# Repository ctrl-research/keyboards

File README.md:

# keyboards
Schematics, pcbs, layout files for all my keyboard projects

## Structure

- `design/` — original keyboard designs, one folder per board with
  `layout/` (KLE, keymap, VIA), `pcb/` (KiCad), `case/` (3DP CAD), and
  `firmware/` (QMK/VIA builds) inside
  - [`gemini/`](design/gemini/) — split staggered 40% that docks into a regular 40%
- `commissions/` — VIA/layout files for boards built for others
- `docs/` — GitHub Pages site with interactive design docs, deployed by
  [`.github/workflows/pages.yml`](.github/workflows/pages.yml) on every push
  to `main` that touches `docs/` (one-time setup: Settings → Pages → Source →
  GitHub Actions)

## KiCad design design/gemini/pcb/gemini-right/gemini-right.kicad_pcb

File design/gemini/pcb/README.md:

# pcb

KiCad projects for the Gemini PCBs — one board per half.

**Architecture (rev A): one controller.** A single Raspberry Pi Pico on the
left half (header-mounted on the back, ~2.5 mm standoff); the right half is
passive with an MCP23017 I/O expander. The halves link over **USB-C
carrying I2C** (3V3/SDA/SCL/GND — any USB 2.0 C-to-C cable). Full pin map,
link wiring, socket-DNP keys and BOM: [`pinmap.md`](pinmap.md).

## Generated projects

- [`gemini-left/`](gemini-left/), [`gemini-right/`](gemini-right/) —
  generated `.kicad_pcb` per half: all footprints placed, nets assigned,
  seam edge cuts drawn. **Unrouted** — routing is interactive work.
- [`gemini-panel/`](gemini-panel/) — **production panel** for JLCPCB/PCBWay:
  both halves in one board, joined along their straight *outer* edges at
  x = 0 with a single **V-score** snap line (the stepped seam can't be
  V-scored — it faces outward and is routed normally). Refs and nets are
  prefixed `L_`/`R_`. Route the individual halves first, then regenerate —
  or route the panel directly and it supersedes them. When ordering: pick
  "panel by customer", 2 designs, and note "V-cut where marked" in remarks.
  Snapped V-score edges land inside the case (the seam-inset walls cover
  all board edges), so no cosmetic cleanup matters.
- Regenerate with KiCad's bundled python (wx workaround included):

  ```
  /Applications/KiCad/KiCad.app/Contents/Frameworks/Python.framework/Versions/Current/bin/python3 tools/gen_kicad_boards.py
  ```

## Inputs (source of truth: `../layout/gemini_docked.kle.json`)

- [`tools/gen_pcb_data.py`](tools/) — derives everything below from the
  layout geometry; [`tools/gen_kicad_boards.py`](tools/) builds the boards.
- [`placement/*_placement.csv`](placement/) — switch centers in mm with
  matrix row/col (per-half origin at its top-left corner).
- [`placement/*_outline.csv`](placement/) — Edge.Cuts vertices in mm
  including the stepped docking seam (inset 1.45 mm from the key boundary —
  the case seam wall carries the true boundary) and the 8 mm rear brow
  (link ports live there). Left ≤ 127.14 × 84.2 mm, right ≤ 122.38 × 84.2 mm.
- [`kbplacer/*_matrix.kle.json`](kbplacer/) — KLE annotated with `row,col`
  legends for the [kbplacer](https://github.com/adamws/kicad-kbplacer)
  plugin.
- [`lib/gemini.pretty`](lib/) — vendored footprints (marbastlib hotswap +
  stabs, Pico, HRO USB-C, MCP23017/passives from KiCad stock) and 3D
  models; licenses in `lib/licenses/`.
- [`gemini.kicad_mod`](gemini.kicad_mod) — source logo artwork from
  bitmap2component (35.9 × 13.9 mm). [`tools/gen_logo_fp.py`](tools/)
  scales it to 6 mm tall and writes `lib/gemini.pretty/Logo_Gemini.kicad_mod`
  with its origin at the artwork centre; the board generator places that
  on **F.SilkS**, centred in the 8 mm rear brow (left x 58.81, right
  x 62.29, both at y −4). The brow's *back* face is full of ports and
  passives, so the front face is where the room is. 6 mm is the practical
  floor for the small "by: j6n" glyphs: it keeps the thinnest stroke at
  0.40 mm and the tightest enclosed counter at 0.22 mm, versus the
  0.15 mm silkscreen minimum JLCPCB/PCBWay quote.

## 3D exports

The docs page's **3D model tab** (`docs/gemini/#model`) renders the full
assembly — boards + case pieces, docked/split and exploded/assembled
(three.js; GLBs live in `docs/gemini/3d/`). Re-export after board changes:

```
kicad-cli pcb export glb --subst-models --include-tracks --include-pads \
  --include-zones --include-silkscreen --user-origin 119.0625x0mm \
  -o raw-left.glb gemini-left/gemini-left.kicad_pcb   # right: no origin arg
npx gltfpack -i raw-left.glb -o docs/gemini/3d/gemini-left.glb -cc -mi -si 0.4 -noq
```

(The +119.0625 mm origin shift puts both halves in one docked frame.
`-noq` matters: quantized output renders at the wrong scale in the viewer.
`--include-silkscreen` costs ~4 % file size and is what makes the brow
logo and the reference designators show up in the viewer.)

## Before fab (rev A checklist)

- [x] Route both boards (autorouted + USB-C escapes rebuilt by hand: the
      generated nested stitch fenced the inner nets on B.Cu, so each link
      /host connector now fans out through 0.6/0.3 vias to F.Cu; DRC: 0
      unconnected on both halves and the panel)
- [ ] Verify HRO USB-C pad↔pin mapping against the datasheet (incl. which
      pads are CC vs SBU — the LED chain crosses on CC)
- [ ] Verify SK6812 MINI-E pad order (assumed 1=VDD 2=DOUT 3=VSS 4=DIN)
- [ ] Host port TP1/TP2 pads: bridge to Pico underside TP3 (D+) / TP2 (D−)
      — decide jumper wires vs relocating pads under the TPs for spring pins
- [ ] Series resistors on link D± so a real charger/host can't hurt anything
- [ ] QMK: cap `RGB_MATRIX_MAXIMUM_BRIGHTNESS` (~120) — 43 LEDs at full
      white would far exceed a 500 mA USB 2.0 budget
- [ ] DRC: Pico pin rows sit at y=19.7 and y=37.5, in the corridors between
      switch rows on both faces — confirm clearances after any nudges
- [ ] Confirm J1 orientation (port opening must overhang the rear edge)
- [ ] Case: ~5 mm pocket under the Pico strip (~2 mm elsewhere), rear
      cutouts for both link ports, side cutout for the Pico micro-USB

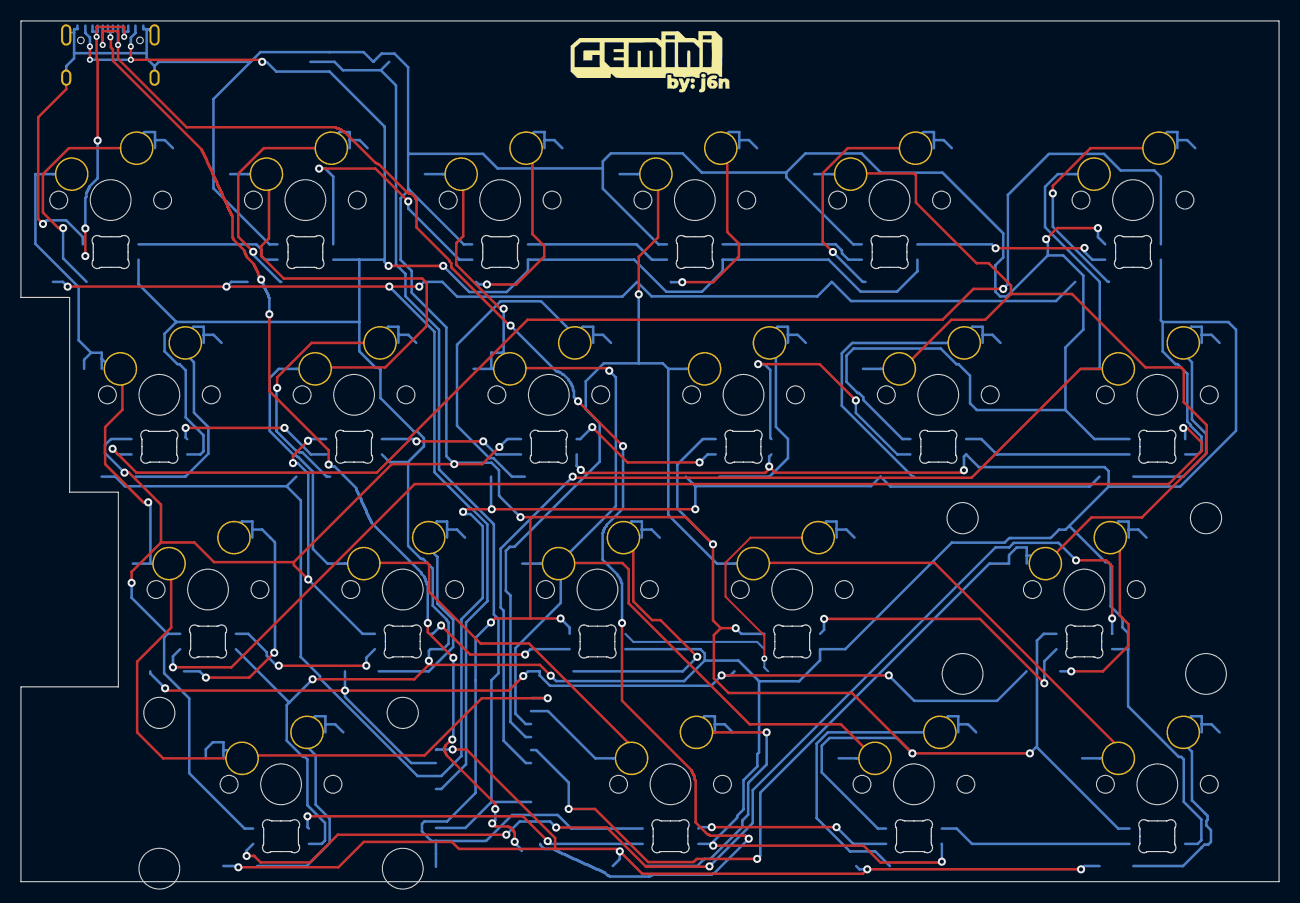
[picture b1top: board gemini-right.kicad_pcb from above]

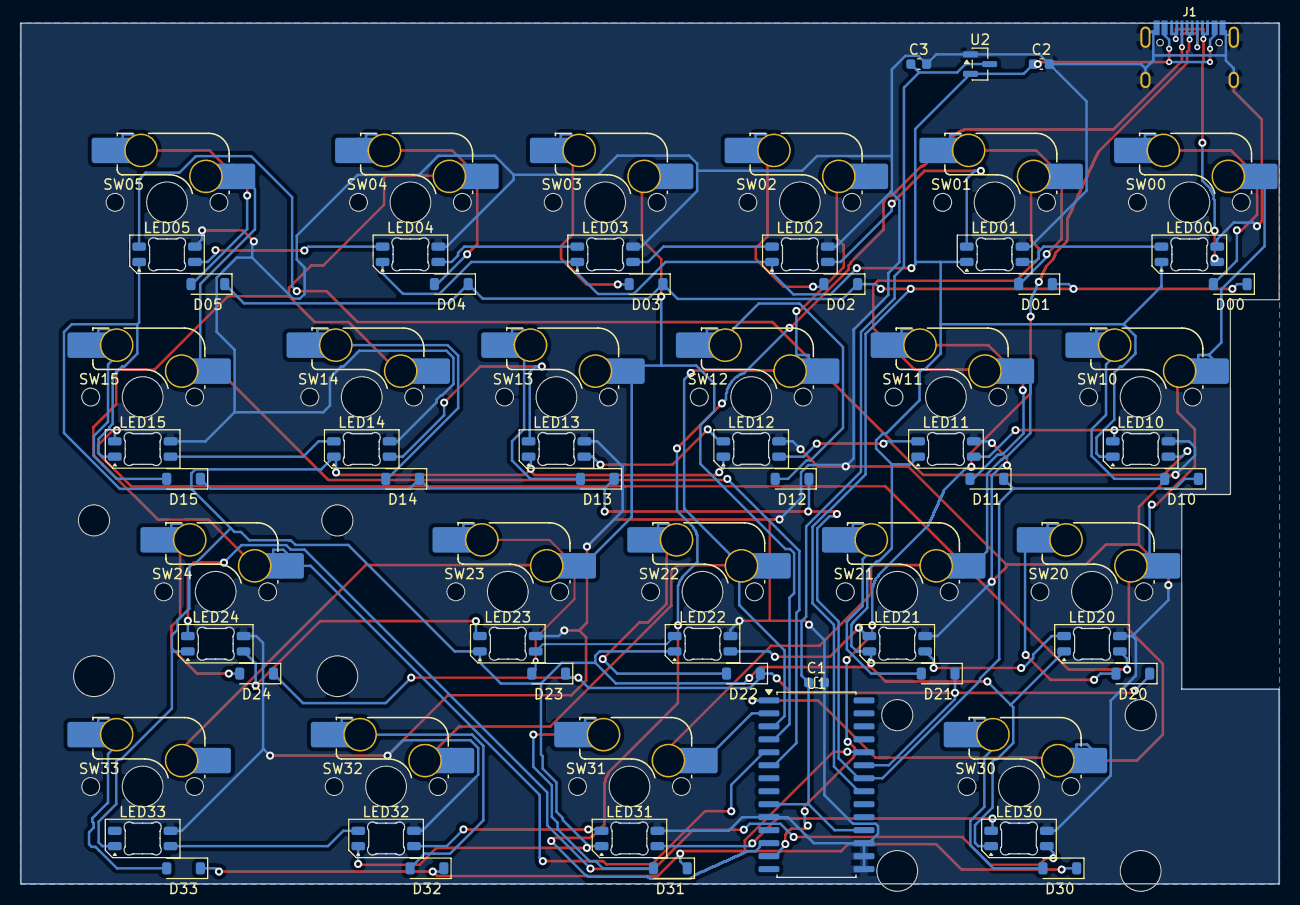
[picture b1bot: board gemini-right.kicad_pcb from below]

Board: 2 copper layers, 123.1 x 84.2 mm, 72 parts (69 on the bottom side), 57 nets.

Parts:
C1: 100nF; C_0603_1608Metric
C2, C3: 1uF; C_0603_1608Metric
D00, D01, D02, D03, D04, D05, D10, D11, D12, D13, D14, D15, D20, D21, D22, D23, D24, D30, D31, D32, D33: 1N4148W; D_SOD-123
G1: Logo_Gemini
J1: USB-C link; HRO-TYPE-C-31-M-12-Assembly
LED00, LED01, LED02, LED03, LED04, LED05, LED10, LED11, LED12, LED13, LED14, LED15, LED20, LED21, LED22, LED23, LED24, LED30, LED31, LED32, LED33: SK6812MINI-E; LED_SK6812MINI-E_3.2x2.8mm_P1.5mm_ReverseMount
ST_SW24: stab 2.0u; STAB_MX_2u
ST_SW30: stab 2.75u; STAB_MX_2.75u
SW00: Y; SW_MX_HS_CPG151101S11_1u
SW01: U; SW_MX_HS_CPG151101S11_1u
SW02: I; SW_MX_HS_CPG151101S11_1u
SW03: O; SW_MX_HS_CPG151101S11_1u
SW04: P; SW_MX_HS_CPG151101S11_1u
SW05: Bksp; SW_MX_HS_CPG151101S11_1.5u
SW10: H; SW_MX_HS_CPG151101S11_1u
SW11: J; SW_MX_HS_CPG151101S11_1u
SW12: K; SW_MX_HS_CPG151101S11_1u
SW13: L; SW_MX_HS_CPG151101S11_1u
SW14: ;; SW_MX_HS_CPG151101S11_1u
SW15: Enter; SW_MX_HS_CPG151101S11_1.25u
SW20: N; SW_MX_HS_CPG151101S11_1u
SW21: M; SW_MX_HS_CPG151101S11_1u
SW22: ,; SW_MX_HS_CPG151101S11_1u
SW23: .; SW_MX_HS_CPG151101S11_1u
SW24: Shift; SW_MX_HS_CPG151101S11_1u
SW30: Space; SW_MX_HS_CPG151101S11_1u
SW31: Fn; SW_MX_HS_CPG151101S11_1.25u
SW32: Alt; SW_MX_HS_CPG151101S11_1.25u
SW33: Ctrl; SW_MX_HS_CPG151101S11_1.25u
U1: MCP23017-E/SO; SOIC-28W_7.5x17.9mm_P1.27mm
U2: MCP1700-3302; SOT-23

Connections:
+3V3: C1.1, C3.1, U1.9, U1.18, U2.3
COL0: SW00.1, SW10.1, SW20.1, SW30.1, U1.1
COL1: SW01.1, SW11.1, SW21.1, SW31.1, U1.2
COL2: SW02.1, SW12.1, SW22.1, SW32.1, U1.3
COL3: SW03.1, SW13.1, SW23.1, SW33.1, U1.4
COL4: SW04.1, SW14.1, SW24.1, U1.5
COL5: SW05.1, SW15.1, U1.6
GND: C1.2, C2.2, C3.2, J1.1, J1.12, J1.13, LED00.3, LED01.3, LED02.3, LED03.3, LED04.3, LED05.3, LED10.3, LED11.3, LED12.3, LED13.3, LED14.3, LED15.3, LED20.3, LED21.3, LED22.3, LED23.3, LED24.3, LED30.3, LED31.3, LED32.3, LED33.3, U1.10, U1.15, U1.16, U1.17, U2.1
LED_CH01: LED00.2, LED01.4
LED_CH02: LED01.2, LED02.4
LED_CH03: LED02.2, LED03.4
LED_CH04: LED03.2, LED04.4
LED_CH05: LED04.2, LED05.4
LED_CH06: LED05.2, LED10.4
LED_CH07: LED10.2, LED11.4
LED_CH08: LED11.2, LED12.4
LED_CH09: LED12.2, LED13.4
LED_CH10: LED13.2, LED14.4
LED_CH11: LED14.2, LED15.4
LED_CH12: LED15.2, LED20.4
LED_CH13: LED20.2, LED21.4
LED_CH14: LED21.2, LED22.4
LED_CH15: LED22.2, LED23.4
LED_CH16: LED23.2, LED24.4
LED_CH17: LED24.2, LED30.4
LED_CH18: LED30.2, LED31.4
LED_CH19: LED31.2, LED32.4
LED_CH20: LED32.2, LED33.4
LED_LINK: J1.3, J1.4, J1.9, J1.10, LED00.4
N_SW00: D00.2, SW00.2
N_SW01: D01.2, SW01.2
N_SW02: D02.2, SW02.2
N_SW03: D03.2, SW03.2
N_SW04: D04.2, SW04.2
N_SW05: D05.2, SW05.2
N_SW10: D10.2, SW10.2
N_SW11: D11.2, SW11.2
N_SW12: D12.2, SW12.2
N_SW13: D13.2, SW13.2
N_SW14: D14.2, SW14.2
N_SW15: D15.2, SW15.2
N_SW20: D20.2, SW20.2
N_SW21: D21.2, SW21.2
N_SW22: D22.2, SW22.2
N_SW23: D23.2, SW23.2
N_SW24: D24.2, SW24.2
N_SW30: D30.2, SW30.2
N_SW31: D31.2, SW31.2
N_SW32: D32.2, SW32.2
N_SW33: D33.2, SW33.2
ROW0: D00.1, D01.1, D02.1, D03.1, D04.1, D05.1, U1.21
ROW1: D10.1, D11.1, D12.1, D13.1, D14.1, D15.1, U1.22
ROW2: D20.1, D21.1, D22.1, D23.1, D24.1, U1.23
ROW3: D30.1, D31.1, D32.1, D33.1, U1.24
SCL: J1.5, J1.8, U1.12
SDA: J1.6, J1.7, U1.13
VSYS: C2.1, J1.2, J1.11, LED00.1, LED01.1, LED02.1, LED03.1, LED04.1, LED05.1, LED10.1, LED11.1, LED12.1, LED13.1, LED14.1, LED15.1, LED20.1, LED21.1, LED22.1, LED23.1, LED24.1, LED30.1, LED31.1, LED32.1, LED33.1, U2.2

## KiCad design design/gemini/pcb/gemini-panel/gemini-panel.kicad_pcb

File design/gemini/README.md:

# Gemini

A split, row-staggered 40% whose two halves dock together to form a regular
staggered 40%. Two boards, one keyboard — hence Gemini (and it's a *mini*).

## Concept

- One Raspberry Pi Pico drives the whole board from the left half; the right
  half is passive (I/O expander) and links over a USB-C cable carrying I2C.
- Apart: a classic two-piece ergo split you can tent and shoulder-width.
- Docked: the halves mate along a staggered seam and become a conventional
  12.75u × 4u 40% (MiniVan-class footprint), visually indistinguishable from a
  one-piece board.
- The row stagger is the joint: the seam steps rightward as it descends, so the
  halves interlock like puzzle pieces instead of meeting at a straight line.

## Docked layout (12.75u × 4u)

```
|Tab  | Q | W | E | R | T ‖ Y | U | I | O | P | Bksp |
|Ctrl  | A | S | D | F | G ‖ H | J | K | L | ; | Ent |
|Shift   | Z | X | C | V | B ‖ N | M | , | . | Shift  |
|Ctl |Gui|Alt |   Space    ‖   Space   | Fn | Alt |Ctl|
```

`‖` marks the seam. Widths are approximate above; exact geometry below.

### Row geometry (units of u, x measured from left edge)

| Row | Left half                                  | Seam x | Right half                                     |
|-----|--------------------------------------------|--------|------------------------------------------------|
| 1   | Tab 1.25 · Q W E R T (5×1u)                | 6.25   | Y U I O P (5×1u) · Bksp 1.5                    |
| 2   | Ctrl 1.5 · A S D F G (5×1u)                | 6.50   | H J K L ; (5×1u) · Enter 1.25                  |
| 3   | Shift 1.75 · Z X C V B (5×1u)              | 6.75   | N M , . (4×1u) · Shift 2                       |
| 4   | Ctrl 1.25 · GUI 1 · Alt 1.25 · Space 2.75  | 6.25   | Space 2.75 · Fn 1.25 · Alt 1.25 · Ctrl 1.25    |

Every row totals 12.75u. Standard row stagger (Tab 1.25 → Ctrl 1.5 → Shift
1.75) so the docked board reads as a normal staggered 40%.

### Seam path

Tracing the boundary of the left half from the top edge down
(coordinates in u, origin at top-left of the docked board):

```
(6.25, 0) → (6.25, 1) → (6.50, 1) → (6.50, 2) → (6.75, 2)
→ (6.75, 3) → (6.25, 3) → (6.25, 4)
```

Rows 1–3 step 0.25u right per row (following the alpha stagger); row 4 steps
back to 6.25 at the split spacebars, giving the right half a 0.5u tooth that
hooks under the left half's row 3 — a natural mechanical interlock.

The PCBs and plates are inset 1.45 mm from this boundary; the **case seam
walls** sit exactly on it and are what actually mate (with embedded
magnets) when the halves dock. See [`case/README.md`](case/README.md).

### Dimensions (1u = 19.05 mm)

| Piece       | Width               | Depth                  |
|-------------|---------------------|------------------------|
| Docked      | 12.75u = 242.9 mm   | 4u + 8 mm brow = 84.2 mm |
| Left half   | 6.25–6.75u = 119.1–128.6 mm | 84.2 mm        |
| Right half  | 6.00–6.50u = 114.3–123.8 mm | 84.2 mm        |

The 8 mm rear "brow" above row 0 hosts the USB-C link ports (and the
Pico's micro-USB reach); the seam runs straight through it at 6.25u. The
key field itself stays exactly 4u deep.

(Plus case wall thickness on the non-seam edges; the seam faces should sit
flush metal-to-metal / plastic-to-plastic.)

## Split & docking mechanism (proposal)

- **Alignment**: the stepped seam self-aligns in x/y; add 2 press-fit dowel
  pins + receivers on the seam faces for z alignment.
- **Retention**: 4–6 pairs of 5×2 mm neodymium magnets embedded in the seam
  faces (polarity keyed so the halves only mate the correct way).
- **Electrical**:
  - One controller: a Raspberry Pi Pico on the left half (header-mounted on
    the back); the right half is passive with an MCP23017 I/O expander.
  - Halves link over **USB-C carrying I2C** (3V3/SDA/SCL/GND) — any USB 2.0
    C-to-C cable, orientation-proof. Works docked and split.
  - Per-key RGB: south-facing SK6812 MINI-E (reverse-mount), one 43-LED
    chain crossing the link on the cable's CC wire.
  - Stretch goal: spring-loaded pogo pins in the row-2/3 seam faces carrying
    the same signals so docking needs no cable at all.
  - Details: [`pcb/pinmap.md`](pcb/pinmap.md).

## Matrix

Both halves are electrically 4×6 (left scanned by the Pico, right read over
I2C via the expander):

| Half  | R1        | R2        | R3        | R4                    |
|-------|-----------|-----------|-----------|------------------------|
| Left  | 6 keys    | 6 keys    | 6 keys    | 4 keys (2 cols unused) |
| Right | 6 keys    | 6 keys    | 5 keys    | 4 keys                 |

## Default keymap

See [`layout/keymap.md`](layout/keymap.md) — Base + Raise (hold right `Fn`)
+ Lower (hold left `Space`) + Adjust, MiniVan conventions, vim arrows on
`HJKL`, full 104-key coverage.

## Keycap compatibility

All sizes are standard: 1u, 1.25u, 1.5u, 1.75u, 2u, 2.75u. Notes:

- 2.75u "spacebars" are usually sold as right-Shift caps — fine in uniform
  profiles (DSA/XDA/KAT uniform); sculpted sets will have R2 shift profile.
- 1.25u Enter is a standard size but a rare legend; blanks or novelty caps.

## Project structure

- [`layout/`](layout/) — KLE layouts (docked + split, importable at
  keyboard-layout-editor.com) and the default keymap layer maps; VIA
  definition lands here too.
- [`pcb/`](pcb/) — KiCad projects for both halves.
- [`case/`](case/) — 3D-printed case CAD + STL/STEP exports.
- [`firmware/`](firmware/) — QMK keyboard definition, VIA support, built
  `.uf2` images.

## Open questions

- [ ] Split space sizes: 2.75/2.75 as drawn, or asymmetric (e.g. 2.25 + Fn on
      left thumb) for a dedicated layer key on the seam?
- [ ] Right Shift 2u vs. 1u Shift + dedicated `/` or `↑`?
- [ ] Pogo pins vs. cable-only for docked mode?
- [ ] Rotary encoder in place of a 1u mod on each half?
- [ ] Case: tray-mount 3DP first article, then CNC alu gasket for v2?

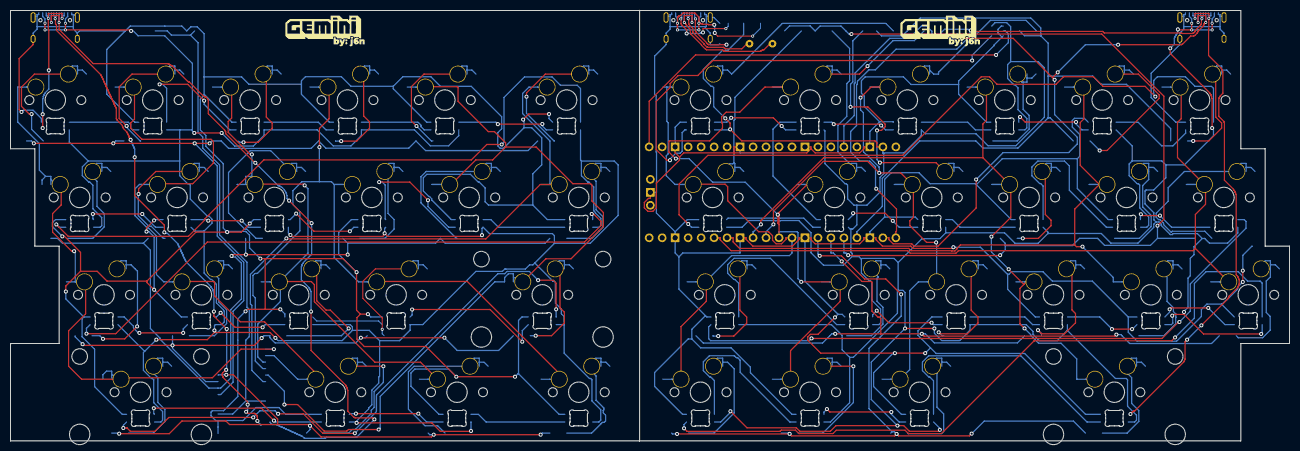
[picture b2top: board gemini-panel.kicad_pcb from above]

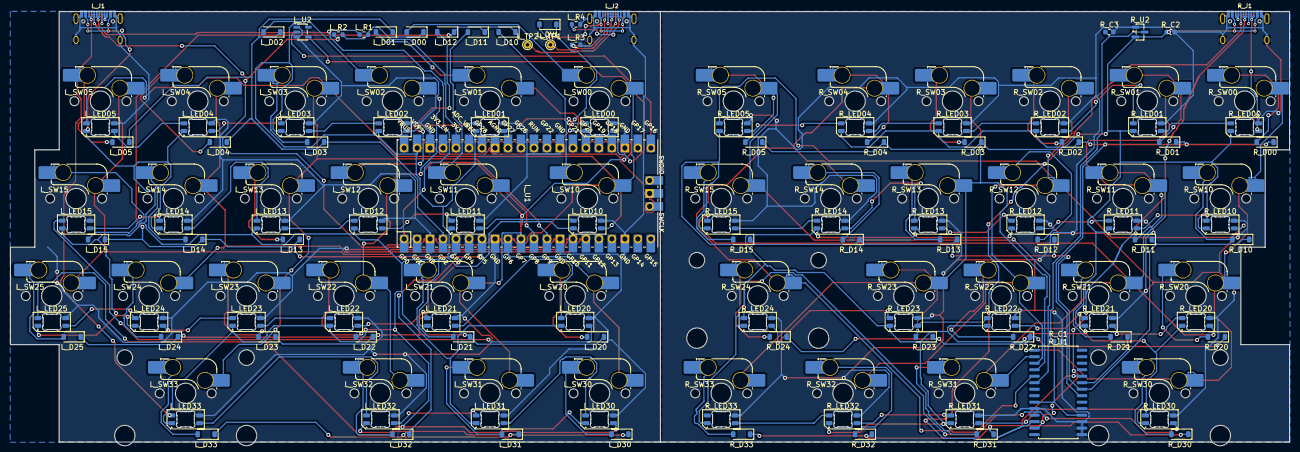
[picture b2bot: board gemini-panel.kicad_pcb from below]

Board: 2 copper layers, 250.2 x 84.2 mm, 151 parts (146 on the bottom side), 123 nets.

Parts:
L_D00, L_D01, L_D02, L_D03, L_D04, L_D05, L_D10, L_D11, L_D12, L_D13, L_D14, L_D15, L_D20, L_D21, L_D22, L_D23, L_D24, L_D25, L_D30, L_D31, L_D32, L_D33: 1N4148W; D_SOD-123
L_DV1: B5819W; D_SOD-123
L_G1: Logo_Gemini
L_J1: USB-C link; HRO-TYPE-C-31-M-12-Assembly
L_J2: USB-C host; HRO-TYPE-C-31-M-12-Assembly
L_LED00, L_LED01, L_LED02, L_LED03, L_LED04, L_LED05, L_LED10, L_LED11, L_LED12, L_LED13, L_LED14, L_LED15, L_LED20, L_LED21, L_LED22, L_LED23, L_LED24, L_LED25, L_LED30, L_LED31, L_LED32, L_LED33: SK6812MINI-E; LED_SK6812MINI-E_3.2x2.8mm_P1.5mm_ReverseMount
L_R1, L_R2: 4k7; R_0603_1608Metric
L_R3, L_R4: 5k1; R_0603_1608Metric
L_ST_SW33: stab 2.75u; STAB_MX_2.75u
L_SW00: Tab; SW_MX_HS_CPG151101S11_1.25u
L_SW01: Q; SW_MX_HS_CPG151101S11_1u
L_SW02: W; SW_MX_HS_CPG151101S11_1u
L_SW03: E; SW_MX_HS_CPG151101S11_1u
L_SW04: R; SW_MX_HS_CPG151101S11_1u
L_SW05: T; SW_MX_HS_CPG151101S11_1u
L_SW10: Esc/Ctrl; SW_MX_HS_CPG151101S11_1.5u
L_SW11: A; SW_MX_HS_CPG151101S11_1u
L_SW12: S; SW_MX_HS_CPG151101S11_1u
L_SW13: D; SW_MX_HS_CPG151101S11_1u
L_SW14: F; SW_MX_HS_CPG151101S11_1u
L_SW15: G; SW_MX_HS_CPG151101S11_1u
L_SW20: Shift; SW_MX_HS_CPG151101S11_1.75u
L_SW21: Z; SW_MX_HS_CPG151101S11_1u
L_SW22: X; SW_MX_HS_CPG151101S11_1u
L_SW23: C; SW_MX_HS_CPG151101S11_1u
L_SW24: V; SW_MX_HS_CPG151101S11_1u
L_SW25: B; SW_MX_HS_CPG151101S11_1u
L_SW30: Ctrl; SW_MX_HS_CPG151101S11_1.25u
L_SW31: GUI; SW_MX_HS_CPG151101S11_1u
L_SW32: Alt; SW_MX_HS_CPG151101S11_1.25u
L_SW33: Space; SW_MX_HS_CPG151101S11_1u
L_TP1: USB_DP; TestPoint_THTPad_D1.5mm_Drill0.7mm
L_TP2: USB_DM; TestPoint_THTPad_D1.5mm_Drill0.7mm
L_U1: Raspberry Pi Pico; RPi_Pico_SMD_TH
L_U2: 74AHCT1G125; SOT-23-5
R_C1: 100nF; C_0603_1608Metric
R_C2, R_C3: 1uF; C_0603_1608Metric
R_D00, R_D01, R_D02, R_D03, R_D04, R_D05, R_D10, R_D11, R_D12, R_D13, R_D14, R_D15, R_D20, R_D21, R_D22, R_D23, R_D24, R_D30, R_D31, R_D32, R_D33: 1N4148W; D_SOD-123
R_G1: Logo_Gemini
R_J1: USB-C link; HRO-TYPE-C-31-M-12-Assembly
R_LED00, R_LED01, R_LED02, R_LED03, R_LED04, R_LED05, R_LED10, R_LED11, R_LED12, R_LED13, R_LED14, R_LED15, R_LED20, R_LED21, R_LED22, R_LED23, R_LED24, R_LED30, R_LED31, R_LED32, R_LED33: SK6812MINI-E; LED_SK6812MINI-E_3.2x2.8mm_P1.5mm_ReverseMount
R_ST_SW24: stab 2.0u; STAB_MX_2u
R_ST_SW30: stab 2.75u; STAB_MX_2.75u
R_SW00: Y; SW_MX_HS_CPG151101S11_1u
R_SW01: U; SW_MX_HS_CPG151101S11_1u
R_SW02: I; SW_MX_HS_CPG151101S11_1u
R_SW03: O; SW_MX_HS_CPG151101S11_1u
R_SW04: P; SW_MX_HS_CPG151101S11_1u
R_SW05: Bksp; SW_MX_HS_CPG151101S11_1.5u
R_SW10: H; SW_MX_HS_CPG151101S11_1u
R_SW11: J; SW_MX_HS_CPG151101S11_1u
R_SW12: K; SW_MX_HS_CPG151101S11_1u
R_SW13: L; SW_MX_HS_CPG151101S11_1u
R_SW14: ;; SW_MX_HS_CPG151101S11_1u
R_SW15: Enter; SW_MX_HS_CPG151101S11_1.25u
R_SW20: N; SW_MX_HS_CPG151101S11_1u
R_SW21: M; SW_MX_HS_CPG151101S11_1u
R_SW22: ,; SW_MX_HS_CPG151101S11_1u
R_SW23: .; SW_MX_HS_CPG151101S11_1u
R_SW24: Shift; SW_MX_HS_CPG151101S11_1u
R_SW30: Space; SW_MX_HS_CPG151101S11_1u
R_SW31: Fn; SW_MX_HS_CPG151101S11_1.25u
R_SW32: Alt; SW_MX_HS_CPG151101S11_1.25u
R_SW33: Ctrl; SW_MX_HS_CPG151101S11_1.25u
R_U1: MCP23017-E/SO; SOIC-28W_7.5x17.9mm_P1.27mm
R_U2: MCP1700-3302; SOT-23

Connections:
L_+3V3: L_R1.2, L_R2.2, L_U1.36
L_CC1: L_J2.4, L_R3.1
L_CC2: L_J2.9, L_R4.1
L_COL0: L_SW00.1, L_SW10.1, L_SW20.1, L_SW30.1, L_U1.9
L_COL1: L_SW01.1, L_SW11.1, L_SW21.1, L_SW31.1, L_U1.10
L_COL2: L_SW02.1, L_SW12.1, L_SW22.1, L_SW32.1, L_U1.11
L_COL3: L_SW03.1, L_SW13.1, L_SW23.1, L_SW33.1, L_U1.12
L_COL4: L_SW04.1, L_SW14.1, L_SW24.1, L_U1.14
L_COL5: L_SW05.1, L_SW15.1, L_SW25.1, L_U1.15
L_GND: L_J1.1, L_J1.12, L_J1.13, L_J2.1, L_J2.12, L_J2.13, L_LED00.3, L_LED01.3, L_LED02.3, L_LED03.3, L_LED04.3, L_LED05.3, L_LED10.3, L_LED11.3, L_LED12.3, L_LED13.3, L_LED14.3, L_LED15.3, L_LED20.3, L_LED21.3, L_LED22.3, L_LED23.3, L_LED24.3, L_LED25.3, L_LED30.3, L_LED31.3, L_LED32.3, L_LED33.3, L_R3.2, L_R4.2, L_U1.3, L_U1.8, L_U1.13, L_U1.18, L_U1.23, L_U1.28, L_U1.33, L_U1.38, L_U1.42, L_U2.1, L_U2.3
L_LED_CH00: L_LED00.4, L_U2.4
L_LED_CH01: L_LED00.2, L_LED01.4
L_LED_CH02: L_LED01.2, L_LED02.4
L_LED_CH03: L_LED02.2, L_LED03.4
L_LED_CH04: L_LED03.2, L_LED04.4
L_LED_CH05: L_LED04.2, L_LED05.4
L_LED_CH06: L_LED05.2, L_LED10.4
L_LED_CH07: L_LED10.2, L_LED11.4
L_LED_CH08: L_LED11.2, L_LED12.4
L_LED_CH09: L_LED12.2, L_LED13.4
L_LED_CH10: L_LED13.2, L_LED14.4
L_LED_CH11: L_LED14.2, L_LED15.4
L_LED_CH12: L_LED15.2, L_LED20.4
L_LED_CH13: L_LED20.2, L_LED21.4
L_LED_CH14: L_LED21.2, L_LED22.4
L_LED_CH15: L_LED22.2, L_LED23.4
L_LED_CH16: L_LED23.2, L_LED24.4
L_LED_CH17: L_LED24.2, L_LED25.4
L_LED_CH18: L_LED25.2, L_LED30.4
L_LED_CH19: L_LED30.2, L_LED31.4
L_LED_CH20: L_LED31.2, L_LED32.4
L_LED_CH21: L_LED32.2, L_LED33.4
L_LED_DATA: L_U1.21, L_U2.2
L_LED_LINK: L_J1.3, L_J1.4, L_J1.9, L_J1.10, L_LED33.2
L_N_SW00: L_D00.2, L_SW00.2
L_N_SW01: L_D01.2, L_SW01.2
L_N_SW02: L_D02.2, L_SW02.2
L_N_SW03: L_D03.2, L_SW03.2
L_N_SW04: L_D04.2, L_SW04.2
L_N_SW05: L_D05.2, L_SW05.2
L_N_SW10: L_D10.2, L_SW10.2
L_N_SW11: L_D11.2, L_SW11.2
L_N_SW12: L_D12.2, L_SW12.2
L_N_SW13: L_D13.2, L_SW13.2
L_N_SW14: L_D14.2, L_SW14.2
L_N_SW15: L_D15.2, L_SW15.2
L_N_SW20: L_D20.2, L_SW20.2
L_N_SW21: L_D21.2, L_SW21.2
L_N_SW22: L_D22.2, L_SW22.2
L_N_SW23: L_D23.2, L_SW23.2
L_N_SW24: L_D24.2, L_SW24.2
L_N_SW25: L_D25.2, L_SW25.2
L_N_SW30: L_D30.2, L_SW30.2
L_N_SW31: L_D31.2, L_SW31.2
L_N_SW32: L_D32.2, L_SW32.2
L_N_SW33: L_D33.2, L_SW33.2
L_ROW0: L_D00.1, L_D01.1, L_D02.1, L_D03.1, L_D04.1, L_D05.1, L_U1.4
L_ROW1: L_D10.1, L_D11.1, L_D12.1, L_D13.1, L_D14.1, L_D15.1, L_U1.5
L_ROW2: L_D20.1, L_D21.1, L_D22.1, L_D23.1, L_D24.1, L_D25.1, L_U1.6
L_ROW3: L_D30.1, L_D31.1, L_D32.1, L_D33.1, L_U1.7
L_SCL: L_J1.5, L_J1.8, L_R2.1, L_U1.2
L_SDA: L_J1.6, L_J1.7, L_R1.1, L_U1.1
L_USB_DM: L_J2.5, L_J2.8, L_TP2.1
L_USB_DP: L_J2.6, L_J2.7, L_TP1.1
L_VBUS_HOST: L_DV1.2, L_J2.2, L_J2.11
L_VSYS: L_DV1.1, L_J1.2, L_J1.11, L_LED00.1, L_LED01.1, L_LED02.1, L_LED03.1, L_LED04.1, L_LED05.1, L_LED10.1, L_LED11.1, L_LED12.1, L_LED13.1, L_LED14.1, L_LED15.1, L_LED20.1, L_LED21.1, L_LED22.1, L_LED23.1, L_LED24.1, L_LED25.1, L_LED30.1, L_LED31.1, L_LED32.1, L_LED33.1, L_U1.39, L_U2.5
R_+3V3: R_C1.1, R_C3.1, R_U1.9, R_U1.18, R_U2.3
R_COL0: R_SW00.1, R_SW10.1, R_SW20.1, R_SW30.1, R_U1.1
R_COL1: R_SW01.1, R_SW11.1, R_SW21.1, R_SW31.1, R_U1.2
R_COL2: R_SW02.1, R_SW12.1, R_SW22.1, R_SW32.1, R_U1.3
R_COL3: R_SW03.1, R_SW13.1, R_SW23.1, R_SW33.1, R_U1.4
R_COL4: R_SW04.1, R_SW14.1, R_SW24.1, R_U1.5
R_COL5: R_SW05.1, R_SW15.1, R_U1.6
R_GND: R_C1.2, R_C2.2, R_C3.2, R_J1.1, R_J1.12, R_J1.13, R_LED00.3, R_LED01.3, R_LED02.3, R_LED03.3, R_LED04.3, R_LED05.3, R_LED10.3, R_LED11.3, R_LED12.3, R_LED13.3, R_LED14.3, R_LED15.3, R_LED20.3, R_LED21.3, R_LED22.3, R_LED23.3, R_LED24.3, R_LED30.3, R_LED31.3, R_LED32.3, R_LED33.3, R_U1.10, R_U1.15, R_U1.16, R_U1.17, R_U2.1
R_LED_CH01: R_LED00.2, R_LED01.4
R_LED_CH02: R_LED01.2, R_LED02.4
R_LED_CH03: R_LED02.2, R_LED03.4
R_LED_CH04: R_LED03.2, R_LED04.4
R_LED_CH05: R_LED04.2, R_LED05.4
R_LED_CH06: R_LED05.2, R_LED10.4
R_LED_CH07: R_LED10.2, R_LED11.4
R_LED_CH08: R_LED11.2, R_LED12.4
R_LED_CH09: R_LED12.2, R_LED13.4
R_LED_CH10: R_LED13.2, R_LED14.4
R_LED_CH11: R_LED14.2, R_LED15.4
R_LED_CH12: R_LED15.2, R_LED20.4
R_LED_CH13: R_LED20.2, R_LED21.4
R_LED_CH14: R_LED21.2, R_LED22.4
R_LED_CH15: R_LED22.2, R_LED23.4
R_LED_CH16: R_LED23.2, R_LED24.4
R_LED_CH17: R_LED24.2, R_LED30.4
R_LED_CH18: R_LED30.2, R_LED31.4
R_LED_CH19: R_LED31.2, R_LED32.4
R_LED_CH20: R_LED32.2, R_LED33.4
R_LED_LINK: R_J1.3, R_J1.4, R_J1.9, R_J1.10, R_LED00.4
R_N_SW00: R_D00.2, R_SW00.2
R_N_SW01: R_D01.2, R_SW01.2
R_N_SW02: R_D02.2, R_SW02.2
R_N_SW03: R_D03.2, R_SW03.2
R_N_SW04: R_D04.2, R_SW04.2
R_N_SW05: R_D05.2, R_SW05.2
R_N_SW10: R_D10.2, R_SW10.2
R_N_SW11: R_D11.2, R_SW11.2
R_N_SW12: R_D12.2, R_SW12.2
R_N_SW13: R_D13.2, R_SW13.2
R_N_SW14: R_D14.2, R_SW14.2
R_N_SW15: R_D15.2, R_SW15.2
R_N_SW20: R_D20.2, R_SW20.2
R_N_SW21: R_D21.2, R_SW21.2
R_N_SW22: R_D22.2, R_SW22.2
R_N_SW23: R_D23.2, R_SW23.2
R_N_SW24: R_D24.2, R_SW24.2
R_N_SW30: R_D30.2, R_SW30.2
R_N_SW31: R_D31.2, R_SW31.2
R_N_SW32: R_D32.2, R_SW32.2
R_N_SW33: R_D33.2, R_SW33.2
R_ROW0: R_D00.1, R_D01.1, R_D02.1, R_D03.1, R_D04.1, R_D05.1, R_U1.21
R_ROW1: R_D10.1, R_D11.1, R_D12.1, R_D13.1, R_D14.1, R_D15.1, R_U1.22
R_ROW2: R_D20.1, R_D21.1, R_D22.1, R_D23.1, R_D24.1, R_U1.23
R_ROW3: R_D30.1, R_D31.1, R_D32.1, R_D33.1, R_U1.24
R_SCL: R_J1.5, R_J1.8, R_U1.12
R_SDA: R_J1.6, R_J1.7, R_U1.13
R_VSYS: R_C2.1, R_J1.2, R_J1.11, R_LED00.1, R_LED01.1, R_LED02.1, R_LED03.1, R_LED04.1, R_LED05.1, R_LED10.1, R_LED11.1, R_LED12.1, R_LED13.1, R_LED14.1, R_LED15.1, R_LED20.1, R_LED21.1, R_LED22.1, R_LED23.1, R_LED24.1, R_LED30.1, R_LED31.1, R_LED32.1, R_LED33.1, R_U2.2

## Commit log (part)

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2026-06-20 add via files
